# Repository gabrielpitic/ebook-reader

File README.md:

# OpenBook - Gabriel Pitic

## Diagrama bloc

## Bill Of Materials (BOM)
| Componenta                 | Link                                                                                                                                                                | Datasheet                                               |
|-----------------------------|-----------------------------------------------------------------------------------------------------------------------------------------------------------------------------|---------------------------------------------------------|
| BD5229G-TR                  | [Mouser](https://ro.mouser.com/ProductDetail/ROHM-Semiconductor/BD5229G-TR?qs=4kLU8WoGk0vvnhrrYwdszw%3D%3D)                                                                 | [Datasheet](https://fscdn.rohm.com/en/products/databook/datasheet/ic/power/voltage_detector/bd52xxg-e.pdf)|
| BME688                      | [Mouser](https://ro.mouser.com/ProductDetail/Bosch-Sensortec/BME688?qs=IS%252B4QmGtzzqQoVDscqwx3A%3D%3D)                                                           | [Datasheet](https://ro.mouser.com/datasheet/2/783/bst_bme688_fl000-2307034.pdf)|
| Bobina                      | [Mouser](https://ro.mouser.com/ProductDetail/Wurth-Elektronik/744043680?qs=PGXP4M47uW6VkZq%252BkzjrHA%3D%3D)                                                                | [Datasheet](https://www.we-online.com/components/products/datasheet/744043680.pdf)|
| Button                      | [Mouser](https://ro.mouser.com/ProductDetail/CK/KMR221GULCLFS?qs=u2NJ%252B70r0goBXaNk7IrU0Q%3D%3D)                                                                          |[Datasheet](https://www.ckswitches.com/media/1479/kmr2.pdf)|
| Capacitor 0.1uF / 50V       | [Farnell](https://ro.farnell.com/multicomp-pro/mcmlr50v104kx7r/ceramic-capacitor-0-1uf-50v-x7r/dp/1600875?srsltid=AfmBOop-NuqSwaWYAsNDvdMnjraBeqfj0sl8f99iLZ_KJc8xpnT4fSqT) | [Datasheet](https://www.farnell.com/datasheets/2873577.pdf?_gl=1*x28a2*_gcl_au*MTYwODAzNzc2OC4xNzQzNDM1MjM4)|
| Capacitor 1uF               | [Mouser](https://ro.mouser.com/ProductDetail/KEMET/C0402C105K9PACTU?qs=UdQET6xYxVCMExqTDkuPeQ%3D%3D)                                                                        | [Datasheet](https://ro.mouser.com/datasheet/2/447/KEM_C1006_X5R_SMD-3316465.pdf)|
| Capacitor 1uF / 50V         | [Mouser](https://ro.mouser.com/ProductDetail/TDK/C1608X7R1H105K080AB?qs=sGAEpiMZZMsh%252B1woXyUXjwVqLNpRsvnQGmKhuYn4DWE%3D)                                                 | [Datasheet](https://product.tdk.com/system/files/dam/doc/product/capacitor/ceramic/mlcc/catalog/mlcc_commercial_general_en.pdf)|
| Capacitor 4.7uF             | [Mouser](https://ro.mouser.com/ProductDetail/KEMET/C0402C475M9PAC7411?qs=cpo3%2FpBou2jRzZxyxJnMGg%3D%3D)                                                                    | [Datasheet](https://ro.mouser.com/datasheet/2/447/KEM_C1006_X5R_SMD-3316465.pdf)|
| Capacitor 4.7uF / 25V       | [Mouser](https://ro.mouser.com/ProductDetail/KYOCERA-AVX/12063C475KAZ2A?qs=%252BdQmOuGyFcG3LdbVp5waMw%3D%3D)                                                                | [Datasheet](https://ro.mouser.com/datasheet/2/40/X7RDielectric-2943470.pdf)|
| Capacitor 10uF              | [Mouser](https://ro.mouser.com/ProductDetail/KEMET/C0402C106M9PACTU?qs=x4XeXhDQKnp%252Bz0lMlwMC3A%3D%3D)                                                                    | [Datasheet](https://ro.mouser.com/datasheet/2/447/KEM_C1006_X5R_SMD-3316465.pdf)|
| Capacitor 100nF             | [Mouser](https://ro.mouser.com/ProductDetail/KEMET/C0402C104K4RAL?qs=pIZUS6sqCWCaMuP2QVR%2Fog%3D%3D)                                                                        | [Datasheet](https://ro.mouser.com/datasheet/2/447/KEM_C1018_X7R_SnPb_SMD-3316276.pdf)|
| Capacitor 100uF TANT        | [Mouser](https://ro.mouser.com/ProductDetail/KYOCERA-AVX/TAJW107M010RNJ?qs=Wtp%252Bf%2FAeVqIH8v1VxV%252B1Rg%3D%3D)                                                          | [Datasheet](https://ro.mouser.com/datasheet/2/40/TAJ-3165264.pdf)|
| Capacitor SUPERCAP          | [Mouser](https://ro.mouser.com/ProductDetail/Seiko-Semiconductors/CPH3225A?qs=3etwrb1wR%252BhUOph6lAO7eg%3D%3D)                                                             | [Datasheet](https://ro.mouser.com/datasheet/2/360/Seiko_Instruments_MicroBattery_E_20230330_2024Jan_-3561061.pdf)|
| CHG_LED                     | [CPC](https://cpc.farnell.com/kingbright/kpg-1608zgc/led-smd-0603-grn/dp/SC20796)                                                                                           | [Datasheet](https://www.farnell.com/datasheets/2046349.pdf)|
| DMG2305UX-7                 | [Mouser](https://ro.mouser.com/ProductDetail/Diodes-Incorporated/DMG2305UX-7?qs=L1DZKBg7t5F%2FNBHrjfxC%252Bg%3D%3D)                                                         | [Datasheet](https://www.diodes.com/assets/Datasheets/DMG2305UX.pdf)|
| DS3231SN#                   | [Mouser](https://ro.mouser.com/ProductDetail/Analog-Devices-Maxim-Integrated/DS3231SN?qs=1eQvB6Dk1vhUlr8%2FOrV0Fw%3D%3D)                                                    | [Datasheet](https://ro.mouser.com/datasheet/2/609/DS3231-3421123.pdf)|
| ESP32-C6-WROOM-1-N8         | [Mouser](https://ro.mouser.com/ProductDetail/Espressif-Systems/ESP32-C6-WROOM-1-N8?qs=8Wlm6%252BaMh8ST02Gmwp74cw%3D%3D)                                                    | [Datasheet](https://ro.mouser.com/datasheet/2/891/Espressif_ESP32_C6_WROOM_1__Datasheet_V0_1_PRELIMI-3239987.pdf)|
| FH34SRJ-24S-0.5SH_99_       | [Mouser](https://ro.mouser.com/ProductDetail/Hirose-Connector/FH34SRJ-24S-0.5SH99?qs=vcbW%252B4%252BSTIpKBl5ap9J8Fw%3D%3D)                                                  | [Datasheet](https://ro.mouser.com/datasheet/2/185/FH34SRJ_24S_0_5SH_99__CL0580_1255_6_99_2DDrawing_0-1615044.pdf)|
| 112A-TAAR-R03_ATTEND        | [LCSC](https://www.lcsc.com/product-detail/SD-Card-Connectors_Attend-Technology-112A-TAAR-R03_C6970445.html)                                                                | [Datasheet](https://www.lcsc.com/datasheet/lcsc_datasheet_2411220717_Attend-Technology-112A-TAAR-R03_C6970445.pdf)|
| MAX17048G+T10               | [Mouser](https://ro.mouser.com/ProductDetail/Analog-Devices-Maxim-Integrated/MAX17048G%2bT10?qs=D7PJwyCwLAoGnnn8jEPRBQ%3D%3D)                                               | [Datasheet](https://ro.mouser.com/datasheet/2/609/MAX17048_MAX17049-3469099.pdf)|
| MBR0530                     | [Mouser](https://ro.mouser.com/ProductDetail/onsemi/MBR0530T3G?qs=3JMERSakebpEmdUS6GetdQ%3D%3D)                                                                             | [Datasheet](https://www.onsemi.com/products/discrete-power-modules/schottky-diodes-schottky-rectifiers/mbr0530t3g)|
| MCP73831                    | [Mouser](https://ro.mouser.com/ProductDetail/Microchip-Technology/MCP73831-2ACI-MC?qs=hH%252BOa0VZEiBneYTVdpuVdg%3D%3D)                                                     | [Datasheet](https://ro.mouser.com/datasheet/2/268/MCP73831_Family_Data_Sheet_DS20001984H-3441711.pdf)|
| PFMF.050.1                  | [Mouser](https://ro.mouser.com/ProductDetail/Schurter/PFMF.050.2?qs=1auRipcfynCums5v1iucSA%3D%3D)                                                                           | [Datasheet](https://ro.mouser.com/datasheet/2/358/typ_PFMF-1275918.pdf)|
| PGB1010603MR                | [Mouser](https://ro.mouser.com/ProductDetail/Littelfuse/PGB1010603MR?qs=gu7KAQ731URLg4GSnNNN7Q%3D%3D)                                                                       | [Datasheet](https://www.littelfuse.com/assetdocs/pulseguard-esd-suppressors-pgb1-datasheet?assetguid=8a337998-d54d-466b-be4e-dc5bcd1f9321)|
| QWIIC_RIGHT_ANGLEA          | [Mouser](https://ro.mouser.com/ProductDetail/JST-Commercial/SM04B-SRSS-TBLFSN?qs=cdbOS8ANM9B3FdyA6cNU2A%3D%3D)                                                              | [Datasheet](https://ro.mouser.com/datasheet/2/564/eSR_SZ-3476820.pdf)|
| Resistor 0.47               | [Mouser](https://ro.mouser.com/ProductDetail/Vishay-Beyschlag/MCT06030C4700FP500?qs=XsZ9OvPb0dt82KlzjdcMjQ%3D%3D)                                                           | [Datasheet](https://www.vishay.com/docs/28705/mcx0x0xpro.pdf)|
| Resistor 2k                 | [Venkel](https://www.venkel.com/part/CR0402-16W-2002FT)                                                                                                                     | [Datasheet](https://data.venkel.com/documents/cr-series?_gl=1*1sqolfs*_ga*MTAzMTIxOTYyMS4xNzQzNzU5MjAy*_ga_JRKGBZNVM8*MTc0Mzc1OTIwMS4xLjEuMTc0Mzc1OTY2OS4zNC4wLjA.)|
| Resistor 5k1                | [Venkel](https://venkel.com/part/CR0402-10W-5101FT)                                                                                                                         | [Datasheet](https://data.venkel.com/documents/cr-series?_gl=1*1e041jc*_ga*MTAzMTIxOTYyMS4xNzQzNzU5MjAy*_ga_JRKGBZNVM8*MTc0Mzc1OTIwMS4xLjEuMTc0Mzc1OTU2Ny41MS4wLjA.)|
| Resistor 10K                | [DigiKey](https://www.digikey.com/en/products/detail/venkel/CR0402-10W-102JT/12332774)                                                                                      | [Datasheet](https://data.venkel.com/documents/cr-series?_gl=1*mn27ew*_ga*MTAzMTIxOTYyMS4xNzQzNzU5MjAy*_ga_JRKGBZNVM8*MTc0Mzc1OTIwMS4xLjAuMTc0Mzc1OTIwMi41OS4wLjA.)|
| Resistor 100K               | [Venkel](https://venkel.com/part/CR0402-16W-1003FT)                                                                                                                         | [Datasheet](https://data.venkel.com/documents/cr-series?_gl=1*oleae1*_ga*MTAzMTIxOTYyMS4xNzQzNzU5MjAy*_ga_JRKGBZNVM8*MTc0Mzc1OTIwMS4xLjEuMTc0Mzc1OTM0My4zNi4wLjA.)|
| SAMACSYS_PARTS_USB4110-GF-A | [Mouser](https://ro.mouser.com/ProductDetail/GCT/USB4110-GF-A?qs=KUoIvG%2F9IlYiZvIXQjyJeA%3D%3D)                                                            | [Datasheet](https://ro.mouser.com/datasheet/2/837/GCT_USB4110_Product_Drawing___20k_cycles-3455479.pdf)|
| SD0805S020S1R0              | [Mouser](https://ro.mouser.com/ProductDetail/KYOCERA-AVX/SD0805S020S1R0?qs=jCA%252BPfw4LHbpkAoSnwrdjw%3D%3D)                                                                | [Datasheet](https://ro.mouser.com/datasheet/2/40/schottky-3165252.pdf)|
| SI1308EDL-T1-GE3            | [Mouser](https://ro.mouser.com/ProductDetail/Vishay-Semiconductors/SI1308EDL-T1-GE3?qs=bX1%252BNvsK%2FBramh9tgpOaEw%3D%3D)                                                  | [Datasheet](https://www.vishay.com/docs/63399/si1308edl.pdf)|
| USBLC6-2SC6Y                | [Mouser](https://ro.mouser.com/ProductDetail/STMicroelectronics/USBLC6-2SC6Y?qs=gNDSiZmRJS%2FOgDexvXkdow%3D%3D)                                                             | [Datasheet](https://ro.mouser.com/datasheet/2/389/usblc6_2sc6y-1852505.pdf)|
| W25Q512JVEIQ                | [Mouser](https://ro.mouser.com/ProductDetail/Winbond/W25Q512JVEIQ?qs=l7cgNqFNU1jw6svr3at6tA%3D%3D)                                                           | [Datasheet](https://ro.mouser.com/datasheet/2/949/Winbond_W25Q512JV_Datasheet-3240039.pdf)|
| XC6220A331MR-G              | [Mouser](https://ro.mouser.com/ProductDetail/Torex-Semiconductor/XC6220A331MR-G?qs=AsjdqWjXhJ8ZSWznL1J0gg%3D%3D)                                                            | [Datasheet](https://ro.mouser.com/datasheet/2/760/xc6220-3371556.pdf)|

## Descrierea Funcționalității Hardware (Arhitectura Hardware)

- **OpenBook** integrează un microcontroler **ESP32-C6** cu suport **WiFi** și **Bluetooth**, care coordonează funcționarea generală a dispozitivului.

- **Alimentarea** se face fie prin **USB-C**, fie printr-o **baterie Li-Po** reîncărcabilă, cu circuite dedicate pentru stabilizarea tensiunii și încărcare în siguranță. 

- **Ecranul e-paper** beneficiază de un sistem separat pentru generarea tensiunilor necesare.

- Dispozitivul dispune de opțiuni variate de conectivitate și extensie: **port USB-C** pentru alimentare și date, **slot microSD** pentru stocare suplimentară, **conector FPC** pentru afișaj și **port Qwiic** pentru senzori adiționali.

- Componente auxiliare precum memoria flash de 64MB, ceasul RTC, senzorul ambiental și circuitul de monitorizare a bateriei contribuie la funcționarea autonomă și adaptabilă a sistemului.

- **Afișaj e-paper** este controlat prin interfață SPI dedicată, cu pini specifici pentru selecție (EPD_CS), reset (EPD_RST), transfer date/comenzi (EPD_DC) și monitorizare stare (EPD_BUSY), oferind astfel o experiență de citire similară cărților tradiționale, cu consum redus de energie.

- **Sistem de butoane** multifuncționale pentru navigare și control, incluzând buton dedicat pentru boot (IO9) și buton pentru schimbarea paginilor (IO15), ce facilitează interacțiunea intuitivă cu dispozitivul.

- **Sistemul RTC (Real-Time Clock)** bazat pe circuitul DS3231SN asigură menținerea orei exacte chiar și când dispozitivul este oprit, cu semnale dedicate pentru întreruperi (INT_RTC) și semnal de ceas de precizie de 32KHz.

- **Managementul energiei** optimizat prin circuitul de monitorizare a bateriei MAX17048G+T10, care permite urmărirea precisă a nivelului de încărcare și estimarea autonomiei rămase.

- **Memoria flash externă** W25Q512JVEIQ de 64MB oferă spațiu amplu pentru stocarea cărților și configurărilor, fiind conectată prin interfață SPI rapidă pentru acces eficient la date.

- **Senzorul ambiental BME688** permite monitorizarea parametrilor de mediu (temperatură, umiditate, presiune și calitatea aerului), adaptând astfel funcționarea dispozitivului la condițiile ambientale.

## Design Log

- Am modificat pozitionarea butoanelor din enclosure pentru a se potrivi cu piesele 3D de pe PCB.
- Am minimizat trecerea intre layere a  traseelor de putere prin trasarea lor inainte de restul rutelor.
- Am adus componentele ce au  mufe de iesire spre exteriorul PCB-ului.

## Pinout ESP32-C6-WROOM-1-N8

| Pin   | Semnal       | Descriere                                          |
|--------|--------------|----------------------------------------------------|
| IO0    | INT_RTC      | Semnal de întrerupere de la modulul RTC           |
| IO1    | 32KHz        | Semnal de 32KHz utilizat ca ceas                  |
| IO2    | MISO         | Comunicație SPI cu cardul SD                      |
| IO3    | EPD_BUSY     | Semnal ocupat de la e-paper                       |
| IO4    | SS_SD        | Selectare card SD                                 |
| IO5    | EPD_DC       | Control date/comandă pentru e-paper               |
| IO6    | SCK          | Semnal SPI Clock                                  |
| IO7    | MOSI         | Semnal SPI Date de ieșire                         |
| IO8    | GPIO8        | Pin general-purpose                               |
| IO9    | IO/BOOT      | Buton pentru inițiere boot                        |
| IO10   | EPD_CS       | Selectare chip pentru e-paper                     |
| IO11   | FLASH_CS     | Selectare chip pentru memoria flash               |
| IO12   | USB_D-       | Comunicație USB (minus)                           |
| IO13   | USB_D+       | Comunicație USB (plus)                            |
| IO15   | IO/CHANGE    | Buton pentru schimbare de pagină                 |
| IO16   | TX           | Transmitere serială (UART)                        |
| IO17   | RX           | Recepție serială (UART)                           |
| IO18   | RTC_RST      | Reset pentru modulul RTC                          |
| IO19   | I2C_PW       | Control alimentare pentru periferice I2C          |
| IO20   | EPD_3V3_C    | Control alimentare e-paper                        |
| IO21   | SDA          | Linie de date I2C                                 |
| IO22   | SCL          | Linie de ceas I2C                                 |
| IO23   | EPD_RST      | Reset pentru e-paper                              |
| EN     | RESET        | Reset general pentru ESP32                        |

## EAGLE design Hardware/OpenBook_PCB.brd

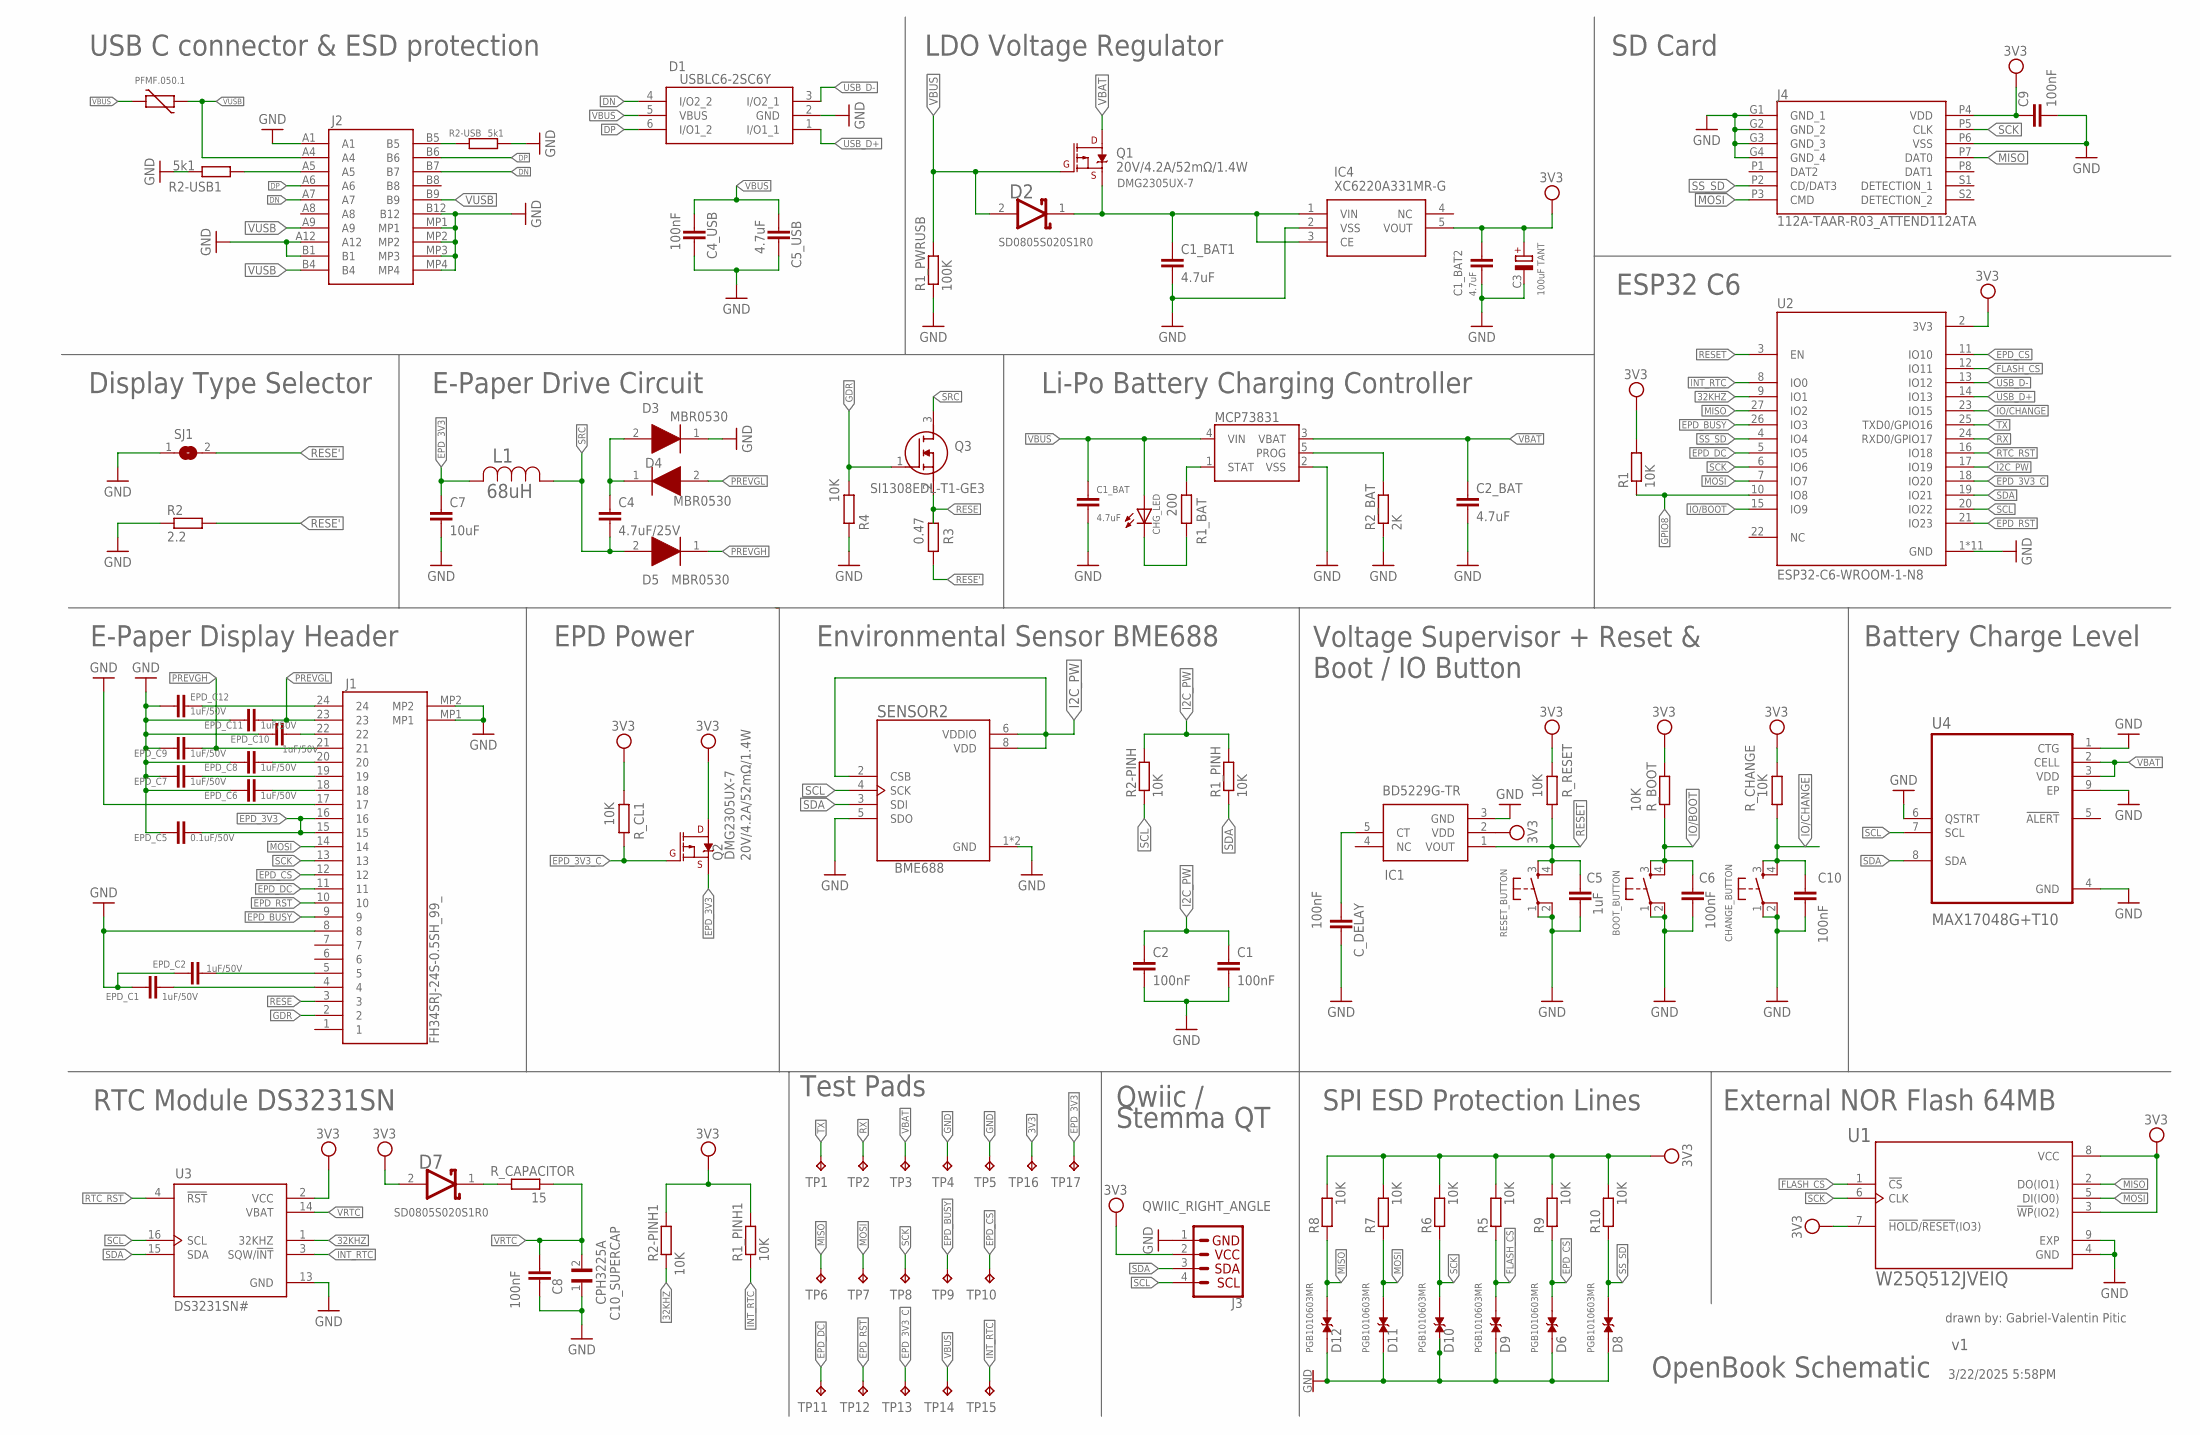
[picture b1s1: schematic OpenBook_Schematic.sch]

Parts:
BOOT_BUTTON: BUTTON_CUSYOMV1; MYBUTTON
C1, C2, C4_USB, C6, C8, C9, C10: 100nF; ESP32_WROVER_EAGLE-LTSPICE_C0402
C1_BAT, C1_BAT1, C1_BAT2, C2_BAT, C5_USB: 4.7uF; ESP32_WROVER_EAGLE-LTSPICE_C0402
C3: 100uF TANT; RCL_CT3528
C4: 4.7uF/25V; ESP32_WROVER_EAGLE-LTSPICE_C0402
C5: 1uF; ESP32_WROVER_EAGLE-LTSPICE_C0402
C7: 10uF; ESP32_WROVER_EAGLE-LTSPICE_C0402
C10_SUPERCAP: CPH3225A; CAPCP3225X100N
CHANGE_BUTTON: BUTTON_CUSYOMV1; MYBUTTON
CHG_LED: ADAFRUIT_LEDCHIP-LED0603; ADAFRUIT_CHIP-LED0603
C_DELAY: 100nF; ESP32_WROVER_EAGLE-LTSPICE_C0402
D1: USBLC6-2SC6Y; SOT95P280X145-6N
D2, D7: ESP32_WROVER_AVX---SD0805S020S1R0_AVX_SD0805S020S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; ESP32_WROVER_AVX---SD0805S020S1R0_AVX_SD0805S020S1R0_0
D3, D4, D5: MBR0530; SOD3716X135N
D6, D8, D9, D10, D11, D12: PGB1010603MR; DIOC1608X36N
EPD_C1, EPD_C2, EPD_C6, EPD_C7, EPD_C8, EPD_C9, EPD_C10, EPD_C11, EPD_C12: 1uF/50V; ESP32_WROVER_EAGLE-LTSPICE_C0402
EPD_C5: 0.1uF/50V; ESP32_WROVER_EAGLE-LTSPICE_C0402
IC1: BD5229G-TR; SOT95P280X125-5N
IC4: XC6220A331MR-G; SOT95P280X120-5N
J1: FH34SRJ-24S-0.5SH_99_; FH34SRJ24S05SH99
J2: SAMACSYS_PARTS_USB4110-GF-A; SAMACSYS_PARTS_USB4110GFA
J3: QWIIC_RIGHT_ANGLE; JST04_1MM_RA
J4: 112A-TAAR-R03_ATTEND112ATA; 112ATAARR03ATTEND
L1: 68uH; IND_4828-WE-TPC_WRE
MCP73831: ESP32_WROVER_SPARKFUN-IC-POWER_MCP73831; ESP32_WROVER_SPARKFUN-IC-POWER_SOT23-5
PFMF.050.1: ESP32C6_VARISTOR; ESP32C6_VARISTOR_CT/CN1812
Q1, Q2: 20V/4.2A/52mΩ/1.4W; ESP32_WROVER_SPARKFUN-DISCRETESEMI_SOT23-3
Q3: SI1308EDL-T1-GE3; SOT65P210X110-3N
R1, R1_PINH, R1_PINH1, R2-PINH, R2-PINH1, R4, R5, R6, R7, R8, R9, R10: 10K; ESP32_WROVER_EAGLE-LTSPICE_R0402
R1_BAT: 200; ESP32_WROVER_EAGLE-LTSPICE_R0402
R1_PWRUSB: 100K; ESP32_WROVER_EAGLE-LTSPICE_R0402
R2: 2.2; ESP32_WROVER_EAGLE-LTSPICE_R0402
R2-USB, R2-USB1: 5k1; ESP32_WROVER_EAGLE-LTSPICE_R0402
R2_BAT: 2K; ESP32_WROVER_EAGLE-LTSPICE_R0402
R3: 0.47; ESP32_WROVER_EAGLE-LTSPICE_R0402
RESET_BUTTON: BUTTON_CUSYOMV1; MYBUTTON
R_BOOT: 10K; ESP32_WROVER_EAGLE-LTSPICE_R0402
R_CAPACITOR: 15; ESP32_WROVER_EAGLE-LTSPICE_R0402
R_CHANGE: 10K; ESP32_WROVER_EAGLE-LTSPICE_R0402
R_CL1: 10K; ESP32_WROVER_EAGLE-LTSPICE_R0402
R_RESET: 10K; ESP32_WROVER_EAGLE-LTSPICE_R0402
SENSOR2: ESP32_WROVER_BME680_BME680; ESP32_WROVER_BME680_PSON80P300X300X100-8N
SJ1: SJ
TP1, TP2, TP3, TP4, TP5, TP6, TP7, TP8, TP9, TP10, TP11, TP12, TP13, TP14, TP15, TP16, TP17: TPTP20R; TP20R
U1: W25Q512JVEIQ; SON50P200X200X80-9N
U2: ESP32-C6-WROOM-1-N8
U3: DS3231SN#; SOIC127P1032X265-16N
U4: MAX17048G+T10; SON50P200X200X80-9N

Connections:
3V3: C1_BAT2.1, C3.+, C9.1, D7.2 (ANODE), IC1.2 (VDD), IC4.5 (VOUT), J3.2, J4.P4 (VDD), Q2.3 (D), R1.2, R1_PINH1.2, R2-PINH1.2, R5.2, R6.2, R7.2, R8.2, R9.2, R10.2, R_BOOT.2, R_CHANGE.2, R_CL1.2, R_RESET.2, TP16.TP, U1.3 (!WP!(IO2)), U1.7 (!HOLD!/!RESET!(IO3)), U1.8 (VCC), U2.2 (3V3), U3.2 (VCC)
32KHZ: R2-PINH1.1, U2.9 (IO1), U3.1 (32KHZ)
A5_J2: J2.A5, R2-USB1.2
B5_J2: J2.B5, R2-USB.1
CE_VIN: C1_BAT1.1, D2.1 (CATHODE), IC4.1 (VIN), IC4.3 (CE), Q1.2 (S)
CHG_STATUS: CHG_LED.C, MCP73831.1 (STAT), R1_BAT.1, R1_BAT.2
C_DELAY: C_DELAY.1, IC1.5 (CT)
D7_R_CAP: D7.1 (CATHODE), R_CAPACITOR.2
DN: D1.4 (I/O2_2), J2.A7, J2.B7
DP: D1.6 (I/O1_2), J2.A6, J2.B6
EPD_3V3: C7.1, EPD_C5.1, J1.15, J1.16, L1.2, Q2.2 (S), TP17.TP
EPD_3V3_C: Q2.1 (G), R_CL1.1, TP13.TP, U2.18 (IO20)
EPD_BUSY: J1.9, TP9.TP, U2.26 (IO3)
EPD_CS: D6.2, J1.12, R9.1, TP10.TP, U2.11 (IO10)
EPD_DC: J1.11, TP11.TP, U2.5 (IO5)
EPD_RST: J1.10, TP12.TP, U2.21 (IO23)
FLASH_CS: D9.2, R5.1, U1.1 (!CS), U2.12 (IO11)
GDR: J1.2, Q3.1 (G), R4.2
GND: BOOT_BUTTON.1, BOOT_BUTTON.2, C1.2, C1_BAT.2, C1_BAT1.2, C1_BAT2.2, C2.2, C2_BAT.2, C3.-, C4_USB.2, C5.2, C5_USB.2, C6.2, C7.2, C8.2, C9.2, C10.2, C10_SUPERCAP.1, CHANGE_BUTTON.1, CHANGE_BUTTON.2, C_DELAY.2, D1.2 (GND), D3.1 (K), D6.1, D8.1, D9.1, D10.1, D11.1, D12.1, EPD_C1.2, EPD_C2.1, EPD_C5.2, EPD_C6.2, EPD_C7.2, EPD_C8.2, EPD_C9.2, EPD_C10.2, EPD_C11.2, EPD_C12.2, IC1.3 (GND), IC4.2 (VSS), J1.8, J1.17, J1.MP1, J1.MP2, J2.A1, J2.A12, J2.B1, J2.B12, J2.MP1, J2.MP2, J2.MP3, J2.MP4, J3.1, J4.G1 (GND_1), J4.G2 (GND_2), J4.G3 (GND_3), J4.G4 (GND_4), J4.P6 (VSS), MCP73831.2 (VSS), R1_PWRUSB.1, R2.1, R2-USB.2, R2-USB1.1, R2_BAT.1, R4.1, RESET_BUTTON.1, RESET_BUTTON.2, SENSOR2.1 (GND), SENSOR2.5 (SDO), SENSOR2.7 (GND), SJ1.1, TP4.TP, TP5.TP, U1.4 (GND), U1.9 (EXP), U2.1 (GND), U2.28 (GND), U2.29_1 (GND), U2.29_2 (GND), U2.29_3 (GND), U2.29_4 (GND), U2.29_5 (GND), U2.29_6 (GND), U2.29_7 (GND), U2.29_8 (GND), U2.29_9 (GND), U3.13 (GND), U4.1 (CTG), U4.4 (GND), U4.6 (QSTRT), U4.9 (EP)
GPIO8: R1.1, U2.10 (IO8)
I2C_PW: C1.1, C2.1, R1_PINH.2, R2-PINH.2, SENSOR2.2 (CSB), SENSOR2.6 (VDDIO), SENSOR2.8 (VDD), U2.17 (IO19)
INT_RTC: R1_PINH1.1, TP15.TP, U2.8 (IO0), U3.3 (SQW/!INT)
IO/BOOT: BOOT_BUTTON.3, BOOT_BUTTON.4, C6.1, R_BOOT.1, U2.15 (IO9)
IO/CHANGE: C10.1, CHANGE_BUTTON.3, CHANGE_BUTTON.4, R_CHANGE.1, U2.23 (IO15)
MISO: D12.2, J4.P7 (DAT0), R8.1, TP6.TP, U1.2 (DO(IO1)), U2.27 (IO2)
MOSI: D11.2, J1.14, J4.P3 (CMD), R7.1, TP7.TP, U1.5 (DI(IO0)), U2.7 (IO7)
unnamed: EPD_C1.1, J1.4
unnamed: EPD_C2.2, J1.5
unnamed: EPD_C6.1, J1.18
unnamed: EPD_C7.1, J1.19
unnamed: EPD_C8.1, J1.20
unnamed: EPD_C10.1, J1.22
unnamed: EPD_C12.1, J1.24
PREVGH: D5.1 (K), EPD_C9.1, J1.21
PREVGL: D4.2 (A), EPD_C11.1, J1.23
PROG: MCP73831.5 (PROG), R2_BAT.2
RESE: J1.3, Q3.2 (S), R3.2
RESE': R2.2, R3.1, SJ1.2
RESET: C5.1, IC1.1 (VOUT), RESET_BUTTON.3, RESET_BUTTON.4, R_RESET.1, U2.3 (EN)
RTC_RST: U2.16 (IO18), U3.4 (!RST)
RX: TP2.TP, U2.24 (RXD0/GPIO17)
SCK: D10.2, J1.13, J4.P5 (CLK), R6.1, TP8.TP, U1.6 (CLK), U2.6 (IO6)
SCL: J3.4, R2-PINH.1, SENSOR2.4 (SCK), U2.20 (IO22), U3.16 (SCL), U4.7 (SCL)
SDA: J3.3, R1_PINH.1, SENSOR2.3 (SDI), U2.19 (IO21), U3.15 (SDA), U4.8 (SDA)
SRC: C4.1, C4.2, D3.2 (A), D4.1 (K), D5.2 (A), L1.1, Q3.3 (D)
SS_SD: D8.2, J4.P2 (CD/DAT3), R10.1, U2.4 (IO4)
TX: TP1.TP, U2.25 (TXD0/GPIO16)
USB_D+: D1.1 (I/O1_1), U2.14 (IO13)
USB_D-: D1.3 (I/O2_1), U2.13 (IO12)
VBAT: C2_BAT.1, MCP73831.3 (VBAT), Q1.3 (D), TP3.TP, U4.2 (CELL), U4.3 (VDD)
VBUS: C1_BAT.1, C4_USB.1, C5_USB.1, CHG_LED.A, D1.5 (VBUS), D2.2 (ANODE), MCP73831.4 (VIN), PFMF.050.1.2, Q1.1 (G), R1_PWRUSB.2, TP14.TP
VRTC: C8.1, C10_SUPERCAP.2, R_CAPACITOR.1, U3.14 (VBAT)
VUSB: J2.A4, J2.A9, J2.B4, J2.B9, PFMF.050.1.1

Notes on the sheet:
USB C connector & ESD protection
LDO Voltage Regulator
SD0805S020S1R0
DMG2305UX-7
SD Card
Display Type Selector
E-Paper Drive Circuit
Li-Po Battery Charging Controller
ESP32 C6
PFMF.050.1
E-Paper Display Header
EPD Power
Environmental Sensor BME688
BME688
Voltage Supervisor + Reset & Boot / IO Button
Battery Charge Level
RTC Module DS3231SN
Test Pads
External NOR Flash 64MB
Qwiic / Stemma QT
SPI ESD Protection Lines
OpenBook Schematic
drawn by: Gabriel-Valentin Pitic
3/22/2025 5:58PM

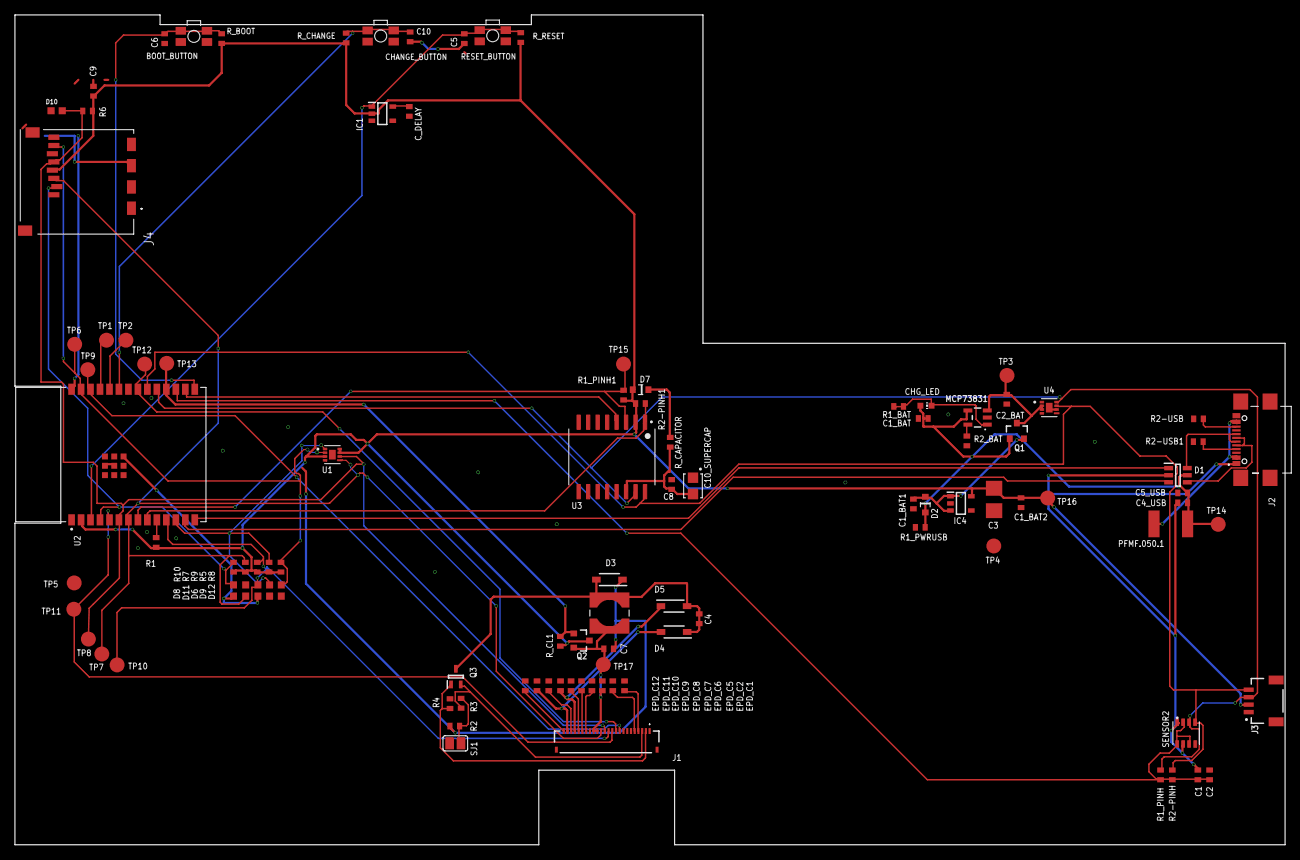
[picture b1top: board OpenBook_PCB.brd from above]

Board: 2 copper layers, 170.2 x 111.2 mm, 103 parts (0 on the bottom side), 53 nets.

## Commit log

2025-04-05 OpenBook: Add most of the files
    Create the file tree for the OpenBook project.
    Add most of the required files.
2025-04-06 Create LICENSE
2025-04-06 Add Block Diagram Image
2025-04-14 Changes after review
2025-04-14 Add .step file back
2025-04-14 Add block diagram in Images/

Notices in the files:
parts and their libraries:
COPYRIGHT: Copyright (C) 2024 Ultra Librarian. All rights reserved.
